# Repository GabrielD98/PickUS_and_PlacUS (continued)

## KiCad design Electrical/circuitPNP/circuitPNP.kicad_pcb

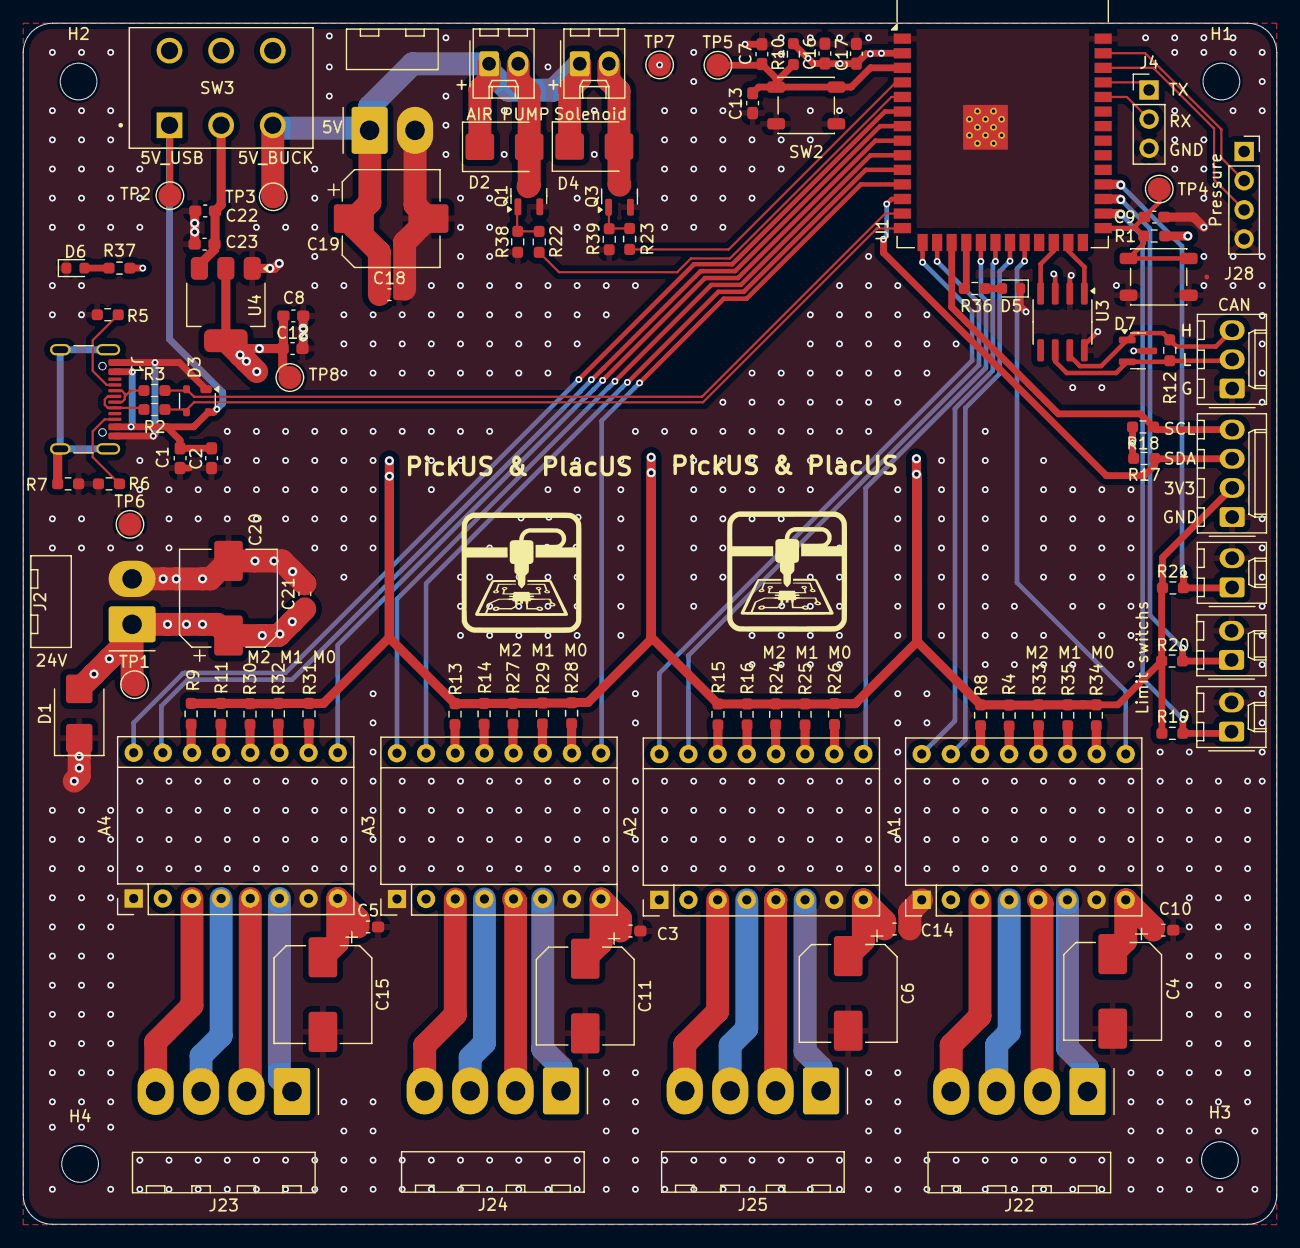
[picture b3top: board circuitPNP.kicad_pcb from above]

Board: 4 copper layers, 109.2 x 104.6 mm, 109 parts (0 on the bottom side), 85 nets.

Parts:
A1, A2, A3, A4: Pololu_Breakout_DRV8825; Pololu_Breakout-16_15.2x20.3mm
C1, C8, C9, C13, C17, C23: 0.1uf; C_0603_1608Metric_Pad1.08x0.95mm_HandSolder
C2, C12, C16, C22: 10uf; C_0603_1608Metric_Pad1.08x0.95mm_HandSolder
C3, C5, C10, C14, C18, C21: 0.1uF; C_0603_1608Metric_Pad1.08x0.95mm_HandSolder
C4, C6, C11, C15, C19, C20: 100uF; CP_Elec_8x10
C7: 1uf/16V 10%; C_0603_1608Metric_Pad1.08x0.95mm_HandSolder
D1: D_TVS; D_SMB
D2, D4: D; D_SMB
D3: SP0503BAHT; SOT-143
D5, D6: LED; LED_0603_1608Metric
D7: NUP2105L; SOT-23
H1, H2, H3, H4: MountingHole; MountingHole_3.2mm_M3
J1: USB_C_Receptacle_USB2.0_16P; USB_C_Receptacle_GCT_USB4105-xx-A_16P_TopMnt_Horizontal
J2, J3: Screw_Terminal_01x02; Molex_KK-396_A-41792-0002_1x02_P3.96mm_Horizontal
J4: Conn_01x03_Pin; PinHeader_1x03_P2.54mm_Vertical
J5, J7, J8, J26, J27: Conn_01x02_Pin; Molex_KK-254_AE-6410-02A_1x02_P2.54mm_Vertical
J6: Conn_01x03_Pin; Molex_KK-254_AE-6410-03A_1x03_P2.54mm_Vertical
J21: Conn_01x04_Pin; Molex_KK-254_AE-6410-04A_1x04_P2.54mm_Vertical
J22, J23, J24, J25: Conn_01x04_Pin; Molex_KK-396_A-41792-0004_1x04_P3.96mm_Horizontal
J28: Conn_01x04_Pin; PinSocket_1x04_P2.54mm_Vertical
Q1, Q3: IRLML6244; SOT-23
R1, R4, R8, R9, R10, R11, R13, R14, R15, R16: 10k 1%; R_0603_1608Metric_Pad0.98x0.95mm_HandSolder
R2, R3: 22; R_0603_1608Metric_Pad0.98x0.95mm_HandSolder
R5, R6: 5.1k; R_0603_1608Metric_Pad0.98x0.95mm_HandSolder
R7: 1; R_0603_1608Metric_Pad0.98x0.95mm_HandSolder
R12: 120; R_0603_1608Metric_Pad0.98x0.95mm_HandSolder
R17, R18: 4.7k; R_0603_1608Metric_Pad0.98x0.95mm_HandSolder
R19, R20, R21, R38, R39: 10k; R_0603_1608Metric_Pad0.98x0.95mm_HandSolder
R22, R23: 100; R_0603_1608Metric_Pad0.98x0.95mm_HandSolder
R24, R25, R26, R27, R28, R29, R30, R31, R32, R33, R34, R35: 0; R_0603_1608Metric_Pad0.98x0.95mm_HandSolder
R36, R37: 330; R_0603_1608Metric_Pad0.98x0.95mm_HandSolder
SW1, SW2: SW_Push; SW_SPST_PTS647_Sx38
SW3: SW_Slide_DPDT; SW_SLW-1678105-6A-N-D
TP1, TP2, TP3, TP4, TP5, TP6, TP7, TP8: TestPoint; TestPoint_Pad_D2.0mm
U1: ESP32-S3-WROOM-1
U3: SN65HVD230; SOIC-8_3.9x4.9mm_P1.27mm
U4: AMS1117-3.3; SOT-223-3_TabPin2

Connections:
/3V3: C8.2, C12.2, C16.2, C17.2, J21.2, J28.1, R1.2, R4.1, R8.1, R9.1, R10.1, R11.1, R13.1, R14.1, R15.1, R16.1, R17.2, R18.2, R19.1, R20.1, R21.1, R24.1, R25.1, R26.1, R27.1, R28.1, R29.1, R30.1, R31.1, R32.1, R33.1, R34.1, R35.1, R37.1, TP8.1, U1.2 (3V3), U3.3 (VCC), U4.2 (VO)
/5V: C22.2, C23.2, SW3.2 (B), U4.3 (VI)
/5V_BUCK: C18.1, C19.1, D2.1 (K), D4.1 (K), J3.1, J26.1, J27.1, SW3.3 (C), TP3.1
/24V: A1.8 (VMOT), A2.8 (VMOT), A3.8 (VMOT), A4.8 (VMOT), C3.1, C4.1, C5.1, C6.1, C10.1, C11.1, C14.1, C15.1, C20.1, C21.1, D1.2 (A2), J2.1, TP1.1
/CANH: D7.1 (K), J6.3, R12.2, U3.7 (CANH)
/CANL: D7.2 (K), J6.2, R12.1, U3.6 (CANL)
/CHIP_PU: C7.1, C13.1, R10.2, SW2.2, TP5.1, U1.3 (EN)
/D+: D3.3 (K), R2.2, U1.14 (USB_D+)
/D-: D3.2 (K), R3.2, U1.13 (USB_D-)
/GPIO0: C9.1, R1.1, SW1.2, TP4.1, U1.27 (IO0)
/GPIO1: J28.2, U1.39 (IO1)
/GPIO2: J28.3, U1.38 (IO2)
/GPIO3: A2.16 (DIR), U1.15 (IO3)
/GPIO4: R23.1, U1.4 (IO4)
/GPIO5: R22.1, U1.5 (IO5)
/GPIO6: A4.16 (DIR), U1.6 (IO6)
/GPIO7: A4.15 (STEP), U1.7 (IO7)
/GPIO10: R36.1, U1.18 (IO10)
/GPIO11: A2.9 (~EN), U1.19 (IO11)
/GPIO12: A1.16 (DIR), U1.20 (IO12)
/GPIO13: A1.15 (STEP), U1.21 (IO13)
/GPIO14: A1.9 (~EN), U1.22 (IO14)
/GPIO15: A4.9 (~EN), U1.8 (IO15)
/GPIO16: A3.16 (DIR), U1.9 (IO16)
/GPIO17: A3.15 (STEP), U1.10 (IO17)
/GPIO18: A3.9 (~EN), U1.11 (IO18)
/GPIO35: J5.1, R19.2, U1.28 (IO35)
/GPIO36: J7.1, R20.2, U1.29 (IO36)
/GPIO37: J8.1, R21.2, U1.30 (IO37)
/GPIO46: A2.15 (STEP), U1.16 (IO46)
/GPIO47: U1.24 (IO47), U3.4 (R)
/GPIO48: U1.25 (IO48), U3.1 (D)
/RX: J4.2, U1.36 (RXD0)
/SCL: J21.4, R18.1, U1.17 (IO9)
/SDA: J21.3, R17.1, U1.12 (IO8)
/TX: J4.1, U1.37 (TXD0)
/VBus: C1.2, C2.2, D3.4 (K), J1.A4 (VBUS), J1.A9 (VBUS), J1.B4 (VBUS), J1.B9 (VBUS), SW3.1 (A), TP2.1
GND: A1.1 (GND), A1.7 (GND), A2.1 (GND), A2.7 (GND), A3.1 (GND), A3.7 (GND), A4.1 (GND), A4.7 (GND), C1.1, C2.1, C3.2, C4.2, C5.2, C6.2, C7.2, C8.1, C9.2, C10.2, C11.2, C12.1, C13.2, C14.2, C15.2, C16.1, C17.1, C18.2, C19.2, C20.2, C21.2, C22.1, C23.1, D1.1 (A1), D3.1 (A), D5.1 (K), D6.1 (K), D7.3 (A), J1.A1 (GND), J1.A12 (GND), J1.B1 (GND), J1.B12 (GND), J2.2, J3.2, J4.3, J5.2, J6.1, J7.2, J8.2, J21.1, J28.4, Q1.2 (S), Q3.2 (S), R5.2, R6.2, R7.2, R38.2, R39.2, SW1.1, SW2.1, TP6.1, TP7.1, U1.1 (GND), U1.40 (GND), U1.41 (GND), U3.2 (GND), U3.8 (Rs), U4.1 (GND)
unnamed: A1.4 (A1), J22.3
unnamed: A1.3 (A2), J22.4
unnamed: A1.5 (B1), J22.2
unnamed: A1.6 (B2), J22.1
unnamed: A1.10 (M0), R34.2
unnamed: A1.11 (M1), R35.2
unnamed: A1.12 (M2), R33.2
unnamed: A1.13 (~RST), R4.2
unnamed: A1.14 (~SLP), R8.2
unnamed: A2.4 (A1), J25.3
unnamed: A2.3 (A2), J25.4
unnamed: A2.5 (B1), J25.2
unnamed: A2.6 (B2), J25.1
unnamed: A2.10 (M0), R26.2
unnamed: A2.11 (M1), R25.2
unnamed: A2.12 (M2), R24.2
unnamed: A2.13 (~RST), R16.2
unnamed: A2.14 (~SLP), R15.2
unnamed: A3.4 (A1), J24.3
unnamed: A3.3 (A2), J24.4
unnamed: A3.5 (B1), J24.2
unnamed: A3.6 (B2), J24.1
unnamed: A3.10 (M0), R28.2
unnamed: A3.11 (M1), R29.2
unnamed: A3.12 (M2), R27.2
unnamed: A3.13 (~RST), R14.2
unnamed: A3.14 (~SLP), R13.2
unnamed: A4.4 (A1), J23.3
unnamed: A4.3 (A2), J23.4
unnamed: A4.5 (B1), J23.2
unnamed: A4.6 (B2), J23.1
unnamed: A4.10 (M0), R31.2
unnamed: A4.11 (M1), R32.2
unnamed: A4.12 (M2), R30.2
unnamed: A4.13 (~RST), R11.2
unnamed: A4.14 (~SLP), R9.2
unnamed: D2.2 (A), J26.2, Q1.3 (D)
unnamed: D4.2 (A), J27.2, Q3.3 (D)
unnamed: D5.2 (A), R36.2
unnamed: D6.2 (A), R37.2
unnamed: J1.A5 (CC1), R5.1
unnamed: J1.B5 (CC2), R6.1
unnamed: J1.A6 (D+), J1.B6 (D+), R2.1
unnamed: J1.A7 (D-), J1.B7 (D-), R3.1
unnamed: J1.S1 (SHIELD), R7.1
unnamed: Q1.1 (G), R22.2, R38.1
unnamed: Q3.1 (G), R23.2, R39.1

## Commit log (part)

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2026-01-14 Create Hardware
2026-01-16 Platformio project creation
2026-01-16 Name change
2026-01-16 Remove after name change
2026-01-16 Complete gitignore
2026-01-16 add gitignore
2026-01-16 kicad project creation
2026-01-16 blue print for test PCB
2026-01-16 add drawio schematic
2026-01-16 wip and gitignore update
2026-01-16 Calibration and mounting hole added to test PCB
2026-01-17 wip, most part are on the circuit, mssing connection
2026-01-17 gitignore update and circuit mostly done, only missing bulck cap value
2026-01-17 Name and logo added to test PCB
2026-01-17 forgot to save file lmao
2026-01-18 only bulck cap value missing, all footprint are selected for a pcb
2026-01-19 circuit done
2026-01-20 pcb wip
2026-01-21 test and images now on correct layer
2026-01-21 edge cut is clean
2026-01-21 fixed error on the ground layer
2026-01-21 test_commit_daph
2026-01-21 pio settings updated
2026-01-21 Position of ref now aligns on board grid
2026-01-21 UML for HMI
2026-01-21 basics for file interpreter implemented
2026-01-21 wip pcb
2026-01-23 pcb done, wainting for circuit testing
2026-01-23 missed that
2026-01-23 pull down on gate for mosfet
2026-01-26 Logic for the storage added
2026-01-26 documentation updated
2026-01-26 fabricationFile for v1
2026-01-26 storage logic tested
2026-01-27 slicer logic implemented
2026-01-27 unit test for file interpreter
2026-01-27 first draft
2026-01-27 unit test for storage
2026-01-27 Fonction moteur
    Premiere fonction de test
2026-01-27 unit test for slicer
2026-01-28 documentation for slicer
2026-01-28 fixed oversight with delta pos on the storage with the slicer
2026-01-28 hmi draft
2026-01-30 wip stateMachine done, mutex next
2026-02-01 update slicer with command dataClass
2026-02-01 File structure and multistepper
    Header file added and 2 motors sync control
2026-02-02 first UI window
2026-02-03 code cleanup, doc in progress
2026-02-03 can load file from desktop in UI
2026-02-03 doc completed
2026-02-03 structure
2026-02-03 Board config and motor array
    Pins in board config and motor array for moveTo
2026-02-03 add back connect and disconnect function
2026-02-03 basic layout implemented
2026-02-03 Controller and data model
    Restructuration around the controller and the data model
2026-02-03 componant can be added to storage from UI
2026-02-04 Controller func basis
2026-02-04 wip communication working
2026-02-04 communication task on core 1
2026-02-10 pressure sensor class working
2026-02-11 DataModel
    Controller and DataModel headers and functions review
2026-02-11 Controller_functions
    completed controller functions
2026-02-11 Updates
    updates to controller functions
2026-02-16 component data can be set for the storage
2026-02-16 A file can now only be analysed once
2026-02-16 test code for MOVE in loop, target{} components in long format and corrected stepper instanciation
    Controller testing and debugging
2026-02-18 jogging widget added
2026-02-18 calbration now a part of adding pieces to storage
2026-02-18 Pick and Place
    First dev of functions
2026-02-18 remove legacy
2026-02-18 run and stop command implemented
2026-02-18 state widget added
2026-02-18 refactoring of gui classes
2026-02-23 some bug fix, board config update, platformio build flag and demo code in main
2026-02-24 Revise README for project details and structure
    Updated project name and expanded README with detailed information about project structure, firmware setup, HMI, electrical components, and dependencies.
2026-02-25 all steps now displayed on the UI
2026-02-25 steps cleared when new slice clicked
2026-02-25 move communication loop into main so communication.hpp and .cpp are now legacy
2026-02-25 missing function prototype
2026-02-26 communcation working and tested on both end
2026-02-26 small fix
2026-02-26 add assert to verify that com data struct keep the right size
2026-02-26 Revert "Merge branch 'Feature/communicationEsp32' of https://github.com/GabrielD98/PickUS_and_PlacUS into Feature/communicationEsp32"
    This reverts commit a8f47d028d8c48deba7b62e96769ae00835378e1, reversing
    changes made to 508c28567d246e0c2429fbe5e21b49e79fbfce82.
2026-03-02 limit switch
2026-03-02 goHome command a control state machine updated
2026-03-03 Global calibration added
2026-03-03 update controller statemachine
2026-03-03 complete ready, moving, and homing state. only missing picking and placing.
2026-03-04 jog logic added
2026-03-04 Fixed buttons enabling order to be more intuitive
2026-03-04 Mosfet class, pick and place states and functions
2026-03-09 control logic added
2026-03-09 connection logic added
2026-03-09 implementation test of pickplace
2026-03-10 fix com delay (add ms to tick conversion)
2026-03-11 change picking logic to use executepickplace and removed legacy code
2026-03-11 Geometry
    New file for integration of physical dimensions and position input conversion
2026-03-11 homing added
2026-03-11 test connection
2026-03-11 rotation and position variation on storage added
2026-03-11 Geometry
    Updated files with implemented functions
2026-03-11 test geometry
    tests for geometry
2026-03-11 connection port handled by gui
2026-03-11 checks for port on every disconnected iteration
2026-03-11 bug fixes
2026-03-11 Physical limitations correction, rescaling in Z
2026-03-11 test for pick place home
2026-03-11 homing intergration tested
2026-03-11 jog mode tested
2026-03-12 Geometry correction and test
2026-03-17 wip geometrie
2026-03-17 fixed storage bug with component position
2026-03-18 geometrie implementation in ctrl, only speed convertion is missing now
2026-03-18 salad easter egg added
2026-03-18 position now displayed with 2 digits
2026-03-18 fix position update freq
2026-03-18 fixed stringed position bug
2026-03-18 fucking macro
2026-03-18 speed correction
2026-03-18 Name change
    Name change for the distance to steps functions
2026-03-18 removed legacy code
2026-03-18 speed
2026-03-18 speed changed
2026-03-18 home speed fix
2026-03-18 fix z axis not moving
2026-03-20 ProperReadMe and elec file cleanup
2026-03-20 fixed display and slicing issue
2026-03-20 geometry fix
2026-03-20 remove going up from pick and place
2026-03-20 fixe picking and placing issue
2026-03-20 fixed offset bug
2026-03-20 TestMove object first draft
    In feature testing
2026-03-21 go to position now more intuitive
    if a user entered a faulty input in the entry, the entry value will be set to the current position insted of refusing the input
2026-03-21 fixed rescaling issue with file loading
2026-03-21 Basic component graph implemented
2026-03-22 Pcb visualization V1
2026-03-22 fix pump never closing
2026-03-23 Addition of tabs to switch between the text positions and the graphic of slicer
2026-03-23 fixed the scrollbar squish bug with latest fixe
2026-03-23 fixes to pcb graph positions
2026-03-23 background image added
2026-03-23 Test objects and relocation under Tests file
2026-03-25 button abstraction WIP
2026-03-25 fixed color bug
2026-03-25 fixed slice position issues
2026-03-25 fixed go to position bug with empty entries
2026-03-25 gui displays the controller state
2026-03-25 switch x and y axis on PnP
2026-03-25 fix x,y swap, and change threshold for pump
2026-03-25 1->4 for z microstepping
2026-03-25 fixed start pause continue features
    doesnt work for homing
2026-03-25 Commentaries, Geometry test correction
    Commentaries on Mosfet and Limitswitch.
2026-03-27 Commentaries on Controller & Geometry
2026-03-27 Connection is now manual and handhsake is now added
2026-03-27 Commentaries on tests (wip)
2026-03-27 z axis change
2026-03-27 modify test for z axis change
2026-03-27 test for pump
2026-03-27 Tests commentaries wip
2026-03-27 calibration can now be loaded from JSON file
2026-03-27 ESP commentaries wip
2026-03-27 limit switch bug fix, change threshold for pressure sensor
2026-03-31 Calibrations can now be saved
2026-03-31 Now UI scan for ESP32 port only
2026-03-31 Fixed position and style of storage window
2026-03-31 removed clamping for yaw
2026-03-31 Rotation added to slicer
2026-03-31 Now all of the storage data is savable for a piece
2026-03-31 Calibration window now centered on opening
2026-03-31 Homing can now occured outside of main UI (bug fixed)
2026-03-31 Rotation now working with slicer
2026-03-31 Error msg window added
2026-03-31 Fixed layout of calibrations
2026-03-31 Now you cant start the PnP without slicing first
2026-04-01 refactored data manager to controller
2026-04-01 highlight_step function description
2026-04-01 Index changes for highlight_step
2026-04-01 Layout changes
2026-04-01 Documentation added for the refactoring
2026-04-01 New tab_widget class
2026-04-01 ESP code documentation WIP, position struct differentiation between step and cartesian
    TestCom and pressureSensor remaining to do document
2026-04-01 Fixed rotation bug
2026-04-03 simplify testRunner to direclty call object.run function
2026-04-03 removed return from nun fonction doc, also moved testCom donc from cpp file to h
2026-04-03 small change in board config
2026-04-03 controller doc review and small fill in positionStep structure to simplify setTarget function
2026-04-03 limit switch doc review
2026-04-03 pressure sensore doc
2026-04-03 oups
2026-04-03 add license
2026-04-03 add stencil for test pcb and update elec documentation
2026-04-03 fix file name in README
2026-04-05 esp 32 md update
2026-04-05 path fix for julius
2026-04-06 Little corrections on documentations
2026-04-09 fixed calibration saves with non-existent file
2026-04-09 Create Mechanical
2026-04-09 merged tested and fixed jog spamming issue
2026-04-09 fixed stop and ending sequence
2026-04-09 Button beautyfier template
2026-04-09 Frame template V1
2026-04-10 documentation for the calibration window
2026-04-10 documentation for the command widget
2026-04-10 documentation for the state widget
2026-04-10 documentation for the slice info widget
2026-04-10 documentation for storage info
2026-04-10 documentation for storage window
2026-04-10 documentation for the jog widget
2026-04-10 New frame around widgets
2026-04-10 documentation for interface
2026-04-10 documentation for controller. Camelcase also universal
2026-04-10 documentation for the utils file
2026-04-11 fixed rotation direction in jog mode
2026-04-11 general doc modifications on multiple files
2026-04-11 UML updated and expanded
2026-04-11 UML added to markdown
2026-04-11 Current step now displayed on UI
2026-04-11 Scroll area now follows the current step
2026-04-11 the step follwer now supports reruns of the PnP
2026-04-11 merge is now runnable, but the slicing doesnt work
    Will hae to be tested with the PnP
2026-04-11 finished frame widged now functioning
2026-04-12 Buttons style and color have been changed
2026-04-15 Buttons update with new format
2026-04-15 Class and State diagrams
2026-04-15 Cleanup and Class Diagram png
2026-04-16 Completed Instructions and STL_Files
2026-04-16 Uptade README.md
2026-04-16 ready for demo
2026-04-16 Finished (for the moment) UI glowup
2026-04-16 read me update
2026-04-25 HomeCommadn done!
2026-04-25 small dix in HomeCommand
2026-04-26 add cstring
2026-04-26 place command implementation done
2026-04-26 moved commands into commands folder
2026-04-28 path fix
2026-05-01 add packed attribut to dataModel
2026-05-02 removed test since big rework is needed, will implement them back later
2026-05-03 logic fix
2026-05-18 fix broken save calib button
2026-05-25 small shange in run for pick and place so its now possible to debug
2026-05-25 add setting window, debug window and manual control of valve and pump
2026-06-01 wip in circuit, moved drive and sensor in new sheet, add global sig
2026-06-02 circuit mostly done!
2026-06-06 wip pcbv2
2026-06-06 final push of the rework, fix homing test, fix multiple start not working
2026-06-16 rooting done, only last check and test missing
2026-06-17 add i bom and fabrication file
2026-06-21 fix: last change before order
2026-06-25 fix: wrong connection on power inpt
2026-06-27 feat: code move task logic into task and add auto realignment
2026-06-27 feat: payload realignement in python
2026-06-28 refactor: remove useless empty
